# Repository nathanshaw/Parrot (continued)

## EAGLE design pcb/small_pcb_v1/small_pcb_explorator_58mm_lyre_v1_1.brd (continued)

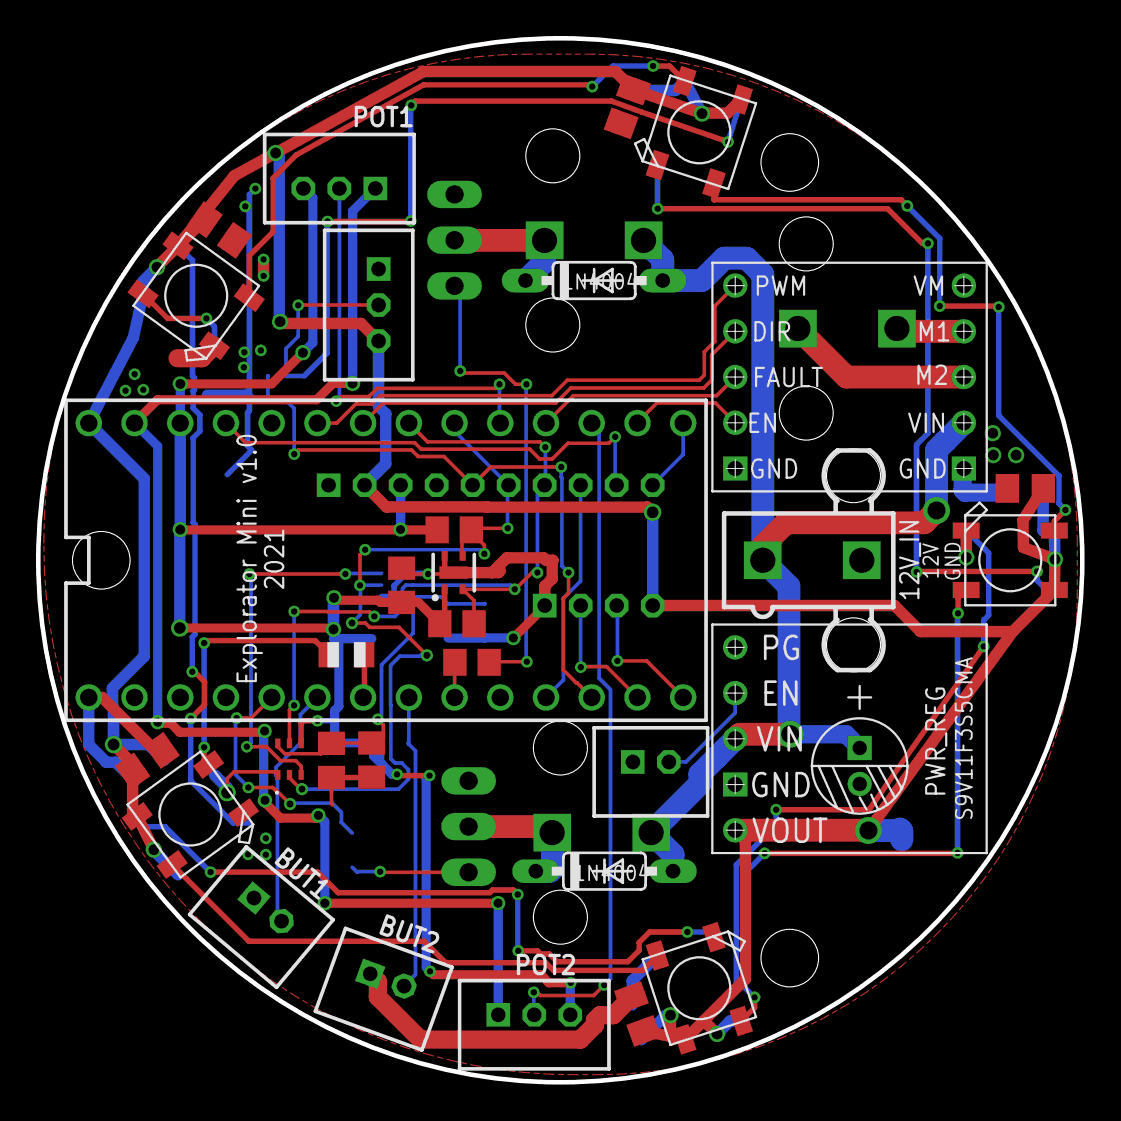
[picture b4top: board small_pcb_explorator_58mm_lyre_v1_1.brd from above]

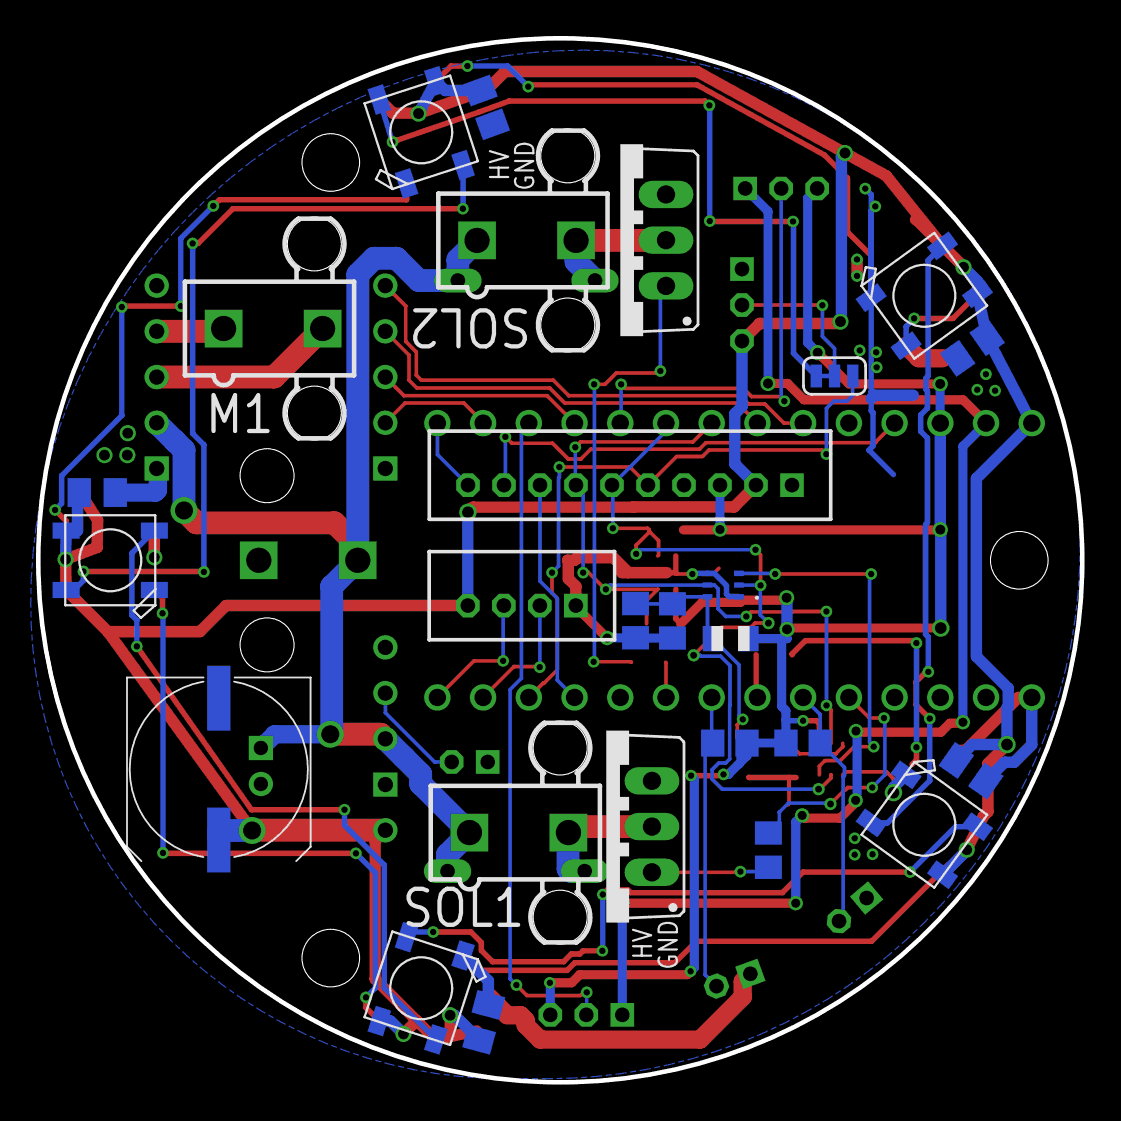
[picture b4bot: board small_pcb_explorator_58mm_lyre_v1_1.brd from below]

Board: 2 copper layers, 58.0 x 58.0 mm, 58 parts (26 on the bottom side), 45 nets.

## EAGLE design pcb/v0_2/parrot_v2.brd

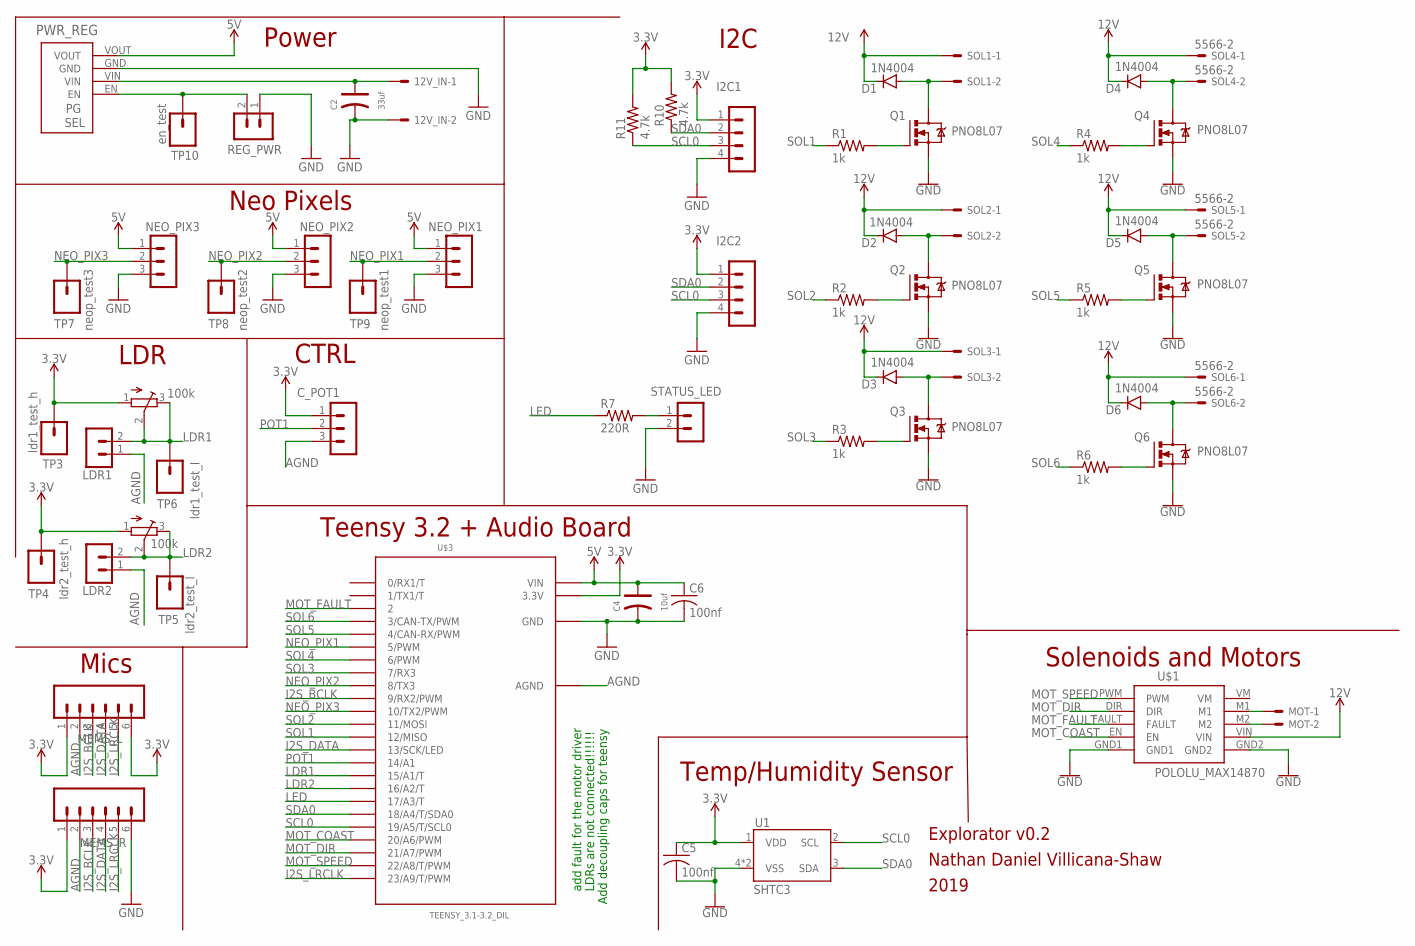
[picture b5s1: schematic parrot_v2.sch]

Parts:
12V_IN: 5566-2
C2: 33uf; PC-D5.3MM
C4: 10uf; PC-D5.3MM
C5, C6: 100nf; C2012
C_POT1: B3B-PH-K
D1, D2, D3, D4, D5, D6: 1N4004; DIODE-1N4001
I2C1, I2C2: B4B-PH-K
LDR1, LDR2: B2B-PH-K
MEMS_L: CONN_06POLAR; MOLEX-1X6
MEMS_R: CONN_06POLAR; MOLEX-1X6
MOT: 5566-2
NEO_PIX1, NEO_PIX2, NEO_PIX3: B3B-PH-K
PWR_REG: S9V11F5S6CMA_MISSINIG_PINS; S9V11F3S5CMA_MISSING_PINS
Q1, Q2, Q3, Q4, Q5, Q6: PNO8L07; TO220BV
R1, R2, R3, R4, R5, R6: 1k; M1206
R7: 220R; M1206
R10, R11: 4.7k; M1206
REG_PWR: B2B-PH-K
SOL1, SOL2, SOL3, SOL4, SOL5, SOL6: 5566-2
STATUS_LED: B2B-PH-K
TM1, TM2: 100k; TC33X
TP3: ldr1_test_h; 1X01
TP4: ldr2_test_h; 1X01
TP5: ldr2_test_l; 1X01
TP6: ldr1_test_l; 1X01
TP7: neop_test3; 1X01
TP8: neop_test2; 1X01
TP9: neop_test1; 1X01
TP10: en_test; 1X01
U1: SHTC3
U$1: POLOLU_MAX14870
U$3: TEENSY_3.1-3.2_DIL; TEENSY_3.0-3.2&LC_DIL

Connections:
3.3V: C5.1, C_POT1.1, I2C1.1, I2C2.1, MEMS_L.1, MEMS_L.6, MEMS_R.1, R10.2, R11.2, TM1.1 (A), TM2.1 (A), TP3.1, TP4.1, U1.1 (VDD), U$3.3.3V
5V: C4.+, C6.1, NEO_PIX1.1, NEO_PIX2.1, NEO_PIX3.1, PWR_REG.VOUT, U$3.VIN
12V: 12V_IN.1, C2.+, D1.C, D2.C, D3.C, D4.C, D5.C, D6.C, PWR_REG.VIN, SOL1.1, SOL2.1, SOL3.1, SOL4.1, SOL5.1, SOL6.1, U$1.VIN
AGND: C_POT1.3, LDR1.1, LDR2.1, MEMS_L.2, MEMS_R.2, U$3.AGND
GND: 12V_IN.2, C2.-, C4.-, C5.2, C6.2, I2C1.4, I2C2.4, MEMS_R.6, NEO_PIX1.3, NEO_PIX2.3, NEO_PIX3.3, PWR_REG.GND, Q1.S, Q2.S, Q3.S, Q4.S, Q5.S, Q6.S, REG_PWR.1, STATUS_LED.2, U1.4 (VSS), U1.5 (VSS), U$1.GND1, U$1.GND2, U$3.GND
I2S_BCLK: MEMS_L.3, MEMS_R.3, U$3.9 (9/RX2/PWM)
I2S_DATA: MEMS_L.4, MEMS_R.4, U$3.13 (13/SCK/LED)
I2S_LRCLK: MEMS_L.5, MEMS_R.5, U$3.23/A9 (23/A9/T/PWM)
LDR1: LDR1.2, TM1.2 (S), TM1.3 (E), TP6.1, U$3.15/A1 (15/A1/T)
LDR2: LDR2.2, TM2.2 (S), TM2.3 (E), TP5.1, U$3.16/A2 (16/A2/T)
LED: R7.1, U$3.17/A3 (17/A3/T)
MOT_COAST: U$1.EN, U$3.20/A6 (20/A6/PWM)
MOT_DIR: U$1.DIR, U$3.21/A7 (21/A7/PWM)
MOT_FAULT: U$1.FAULT, U$3.2
MOT_SPEED: U$1.PWM, U$3.22/A8 (22/A8/T/PWM)
unnamed: Q5.G, R5.2
unnamed: D5.A, Q5.D, SOL5.2
unnamed: Q6.G, R6.2
unnamed: Q2.G, R2.2
unnamed: D6.A, Q6.D, SOL6.2
unnamed: R7.2, STATUS_LED.1
unnamed: D2.A, Q2.D, SOL2.2
unnamed: PWR_REG.EN, REG_PWR.2, TP10.1
unnamed: Q3.G, R3.2
unnamed: D3.A, Q3.D, SOL3.2
unnamed: Q4.G, R4.2
unnamed: D4.A, Q4.D, SOL4.2
unnamed: Q1.G, R1.2
unnamed: D1.A, Q1.D, SOL1.2
unnamed: MOT.2, U$1.M2
unnamed: MOT.1, U$1.M1
NEO_PIX1: NEO_PIX1.2, TP9.1, U$3.5 (5/PWM)
NEO_PIX2: NEO_PIX2.2, TP8.1, U$3.8 (8/TX3)
NEO_PIX3: NEO_PIX3.2, TP7.1, U$3.10 (10/TX2/PWM)
POT1: C_POT1.2, U$3.14/A0 (14/A1)
SCL0: I2C1.3, I2C2.3, R11.1, U1.2 (SCL), U$3.19/A5 (19/A5/T/SCL0)
SDA0: I2C1.2, I2C2.2, R10.1, U1.3 (SDA), U$3.18/A4 (18/A4/T/SDA0)
SOL1: R1.1, U$3.12 (12/MISO)
SOL2: R2.1, U$3.11 (11/MOSI)
SOL3: R3.1, U$3.7 (7/RX3)
SOL4: R4.1, U$3.6 (6/PWM)
SOL5: R5.1, U$3.4 (4/CAN-RX/PWM)
SOL6: R6.1, U$3.3 (3/CAN-TX/PWM)

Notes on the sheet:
Neo Pixels
LDR
I2C
Solenoids and Motors
Teensy 3.2 + Audio Board
Mics
Power
Temp/Humidity Sensor
CTRL
add fault for the motor driver
LDRs are not connected!!!!!!
Add decoupling caps for teensy
Explorator v0.2
Nathan Daniel Villicana-Shaw
2019

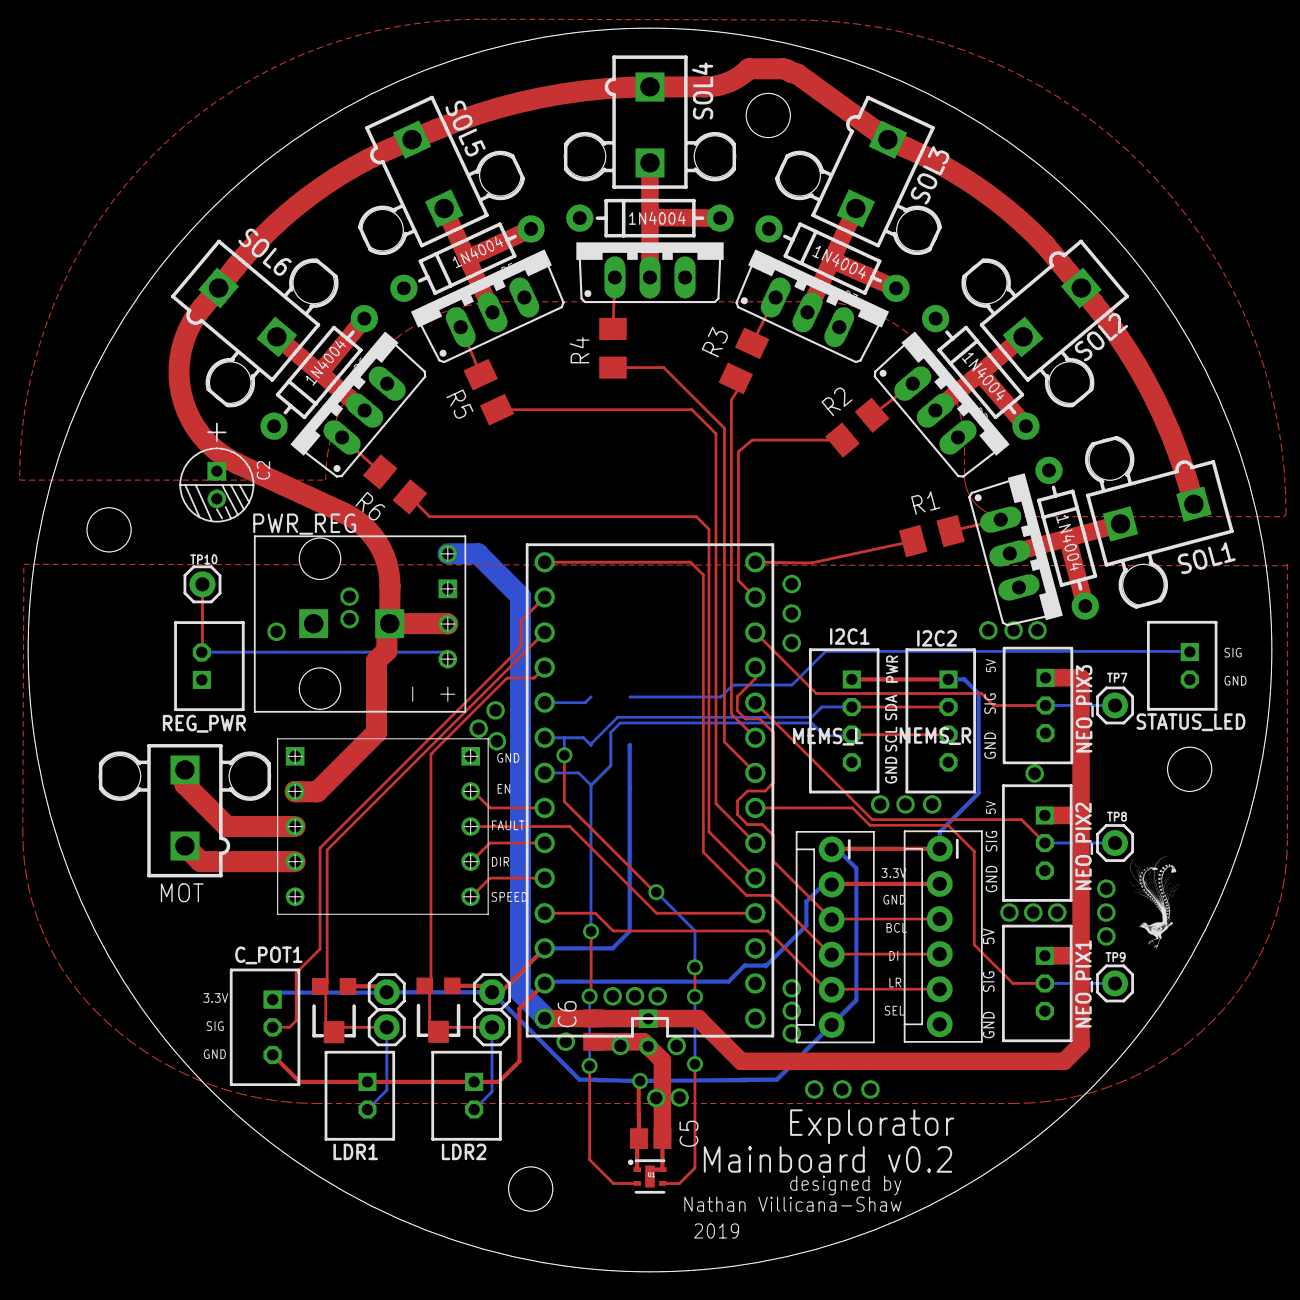
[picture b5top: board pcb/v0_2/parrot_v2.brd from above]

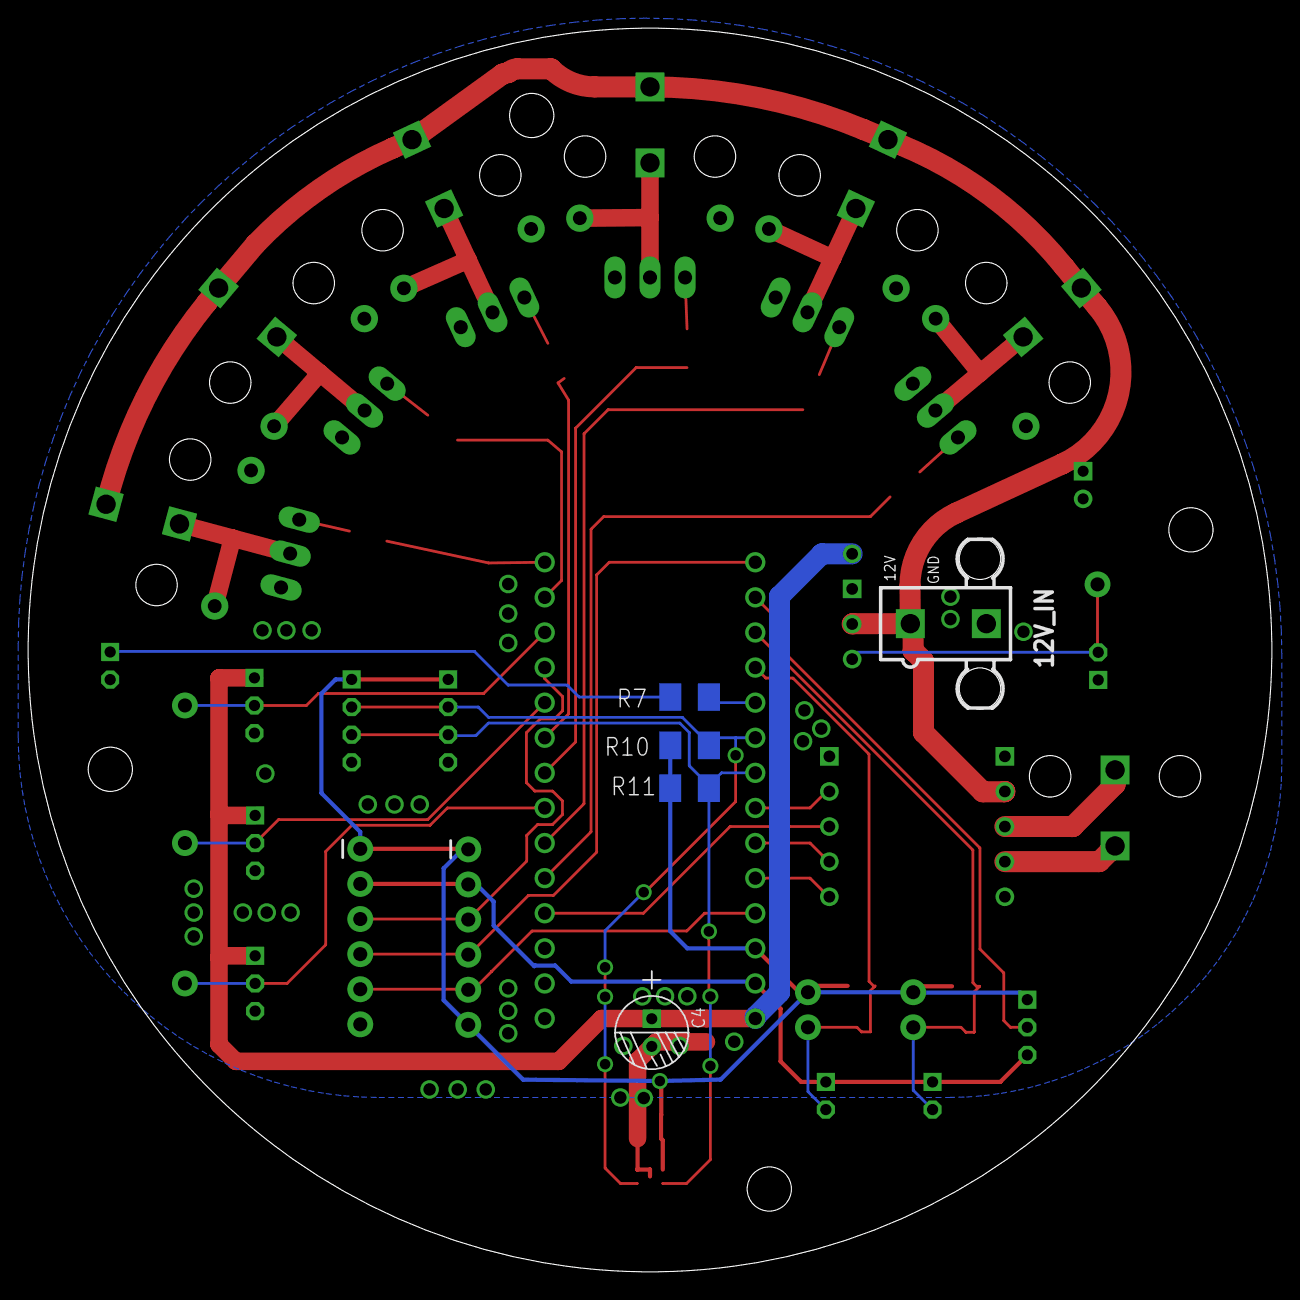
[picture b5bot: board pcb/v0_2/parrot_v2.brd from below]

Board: 2 copper layers, 90.0 x 90.0 mm, 59 parts (5 on the bottom side), 43 nets.

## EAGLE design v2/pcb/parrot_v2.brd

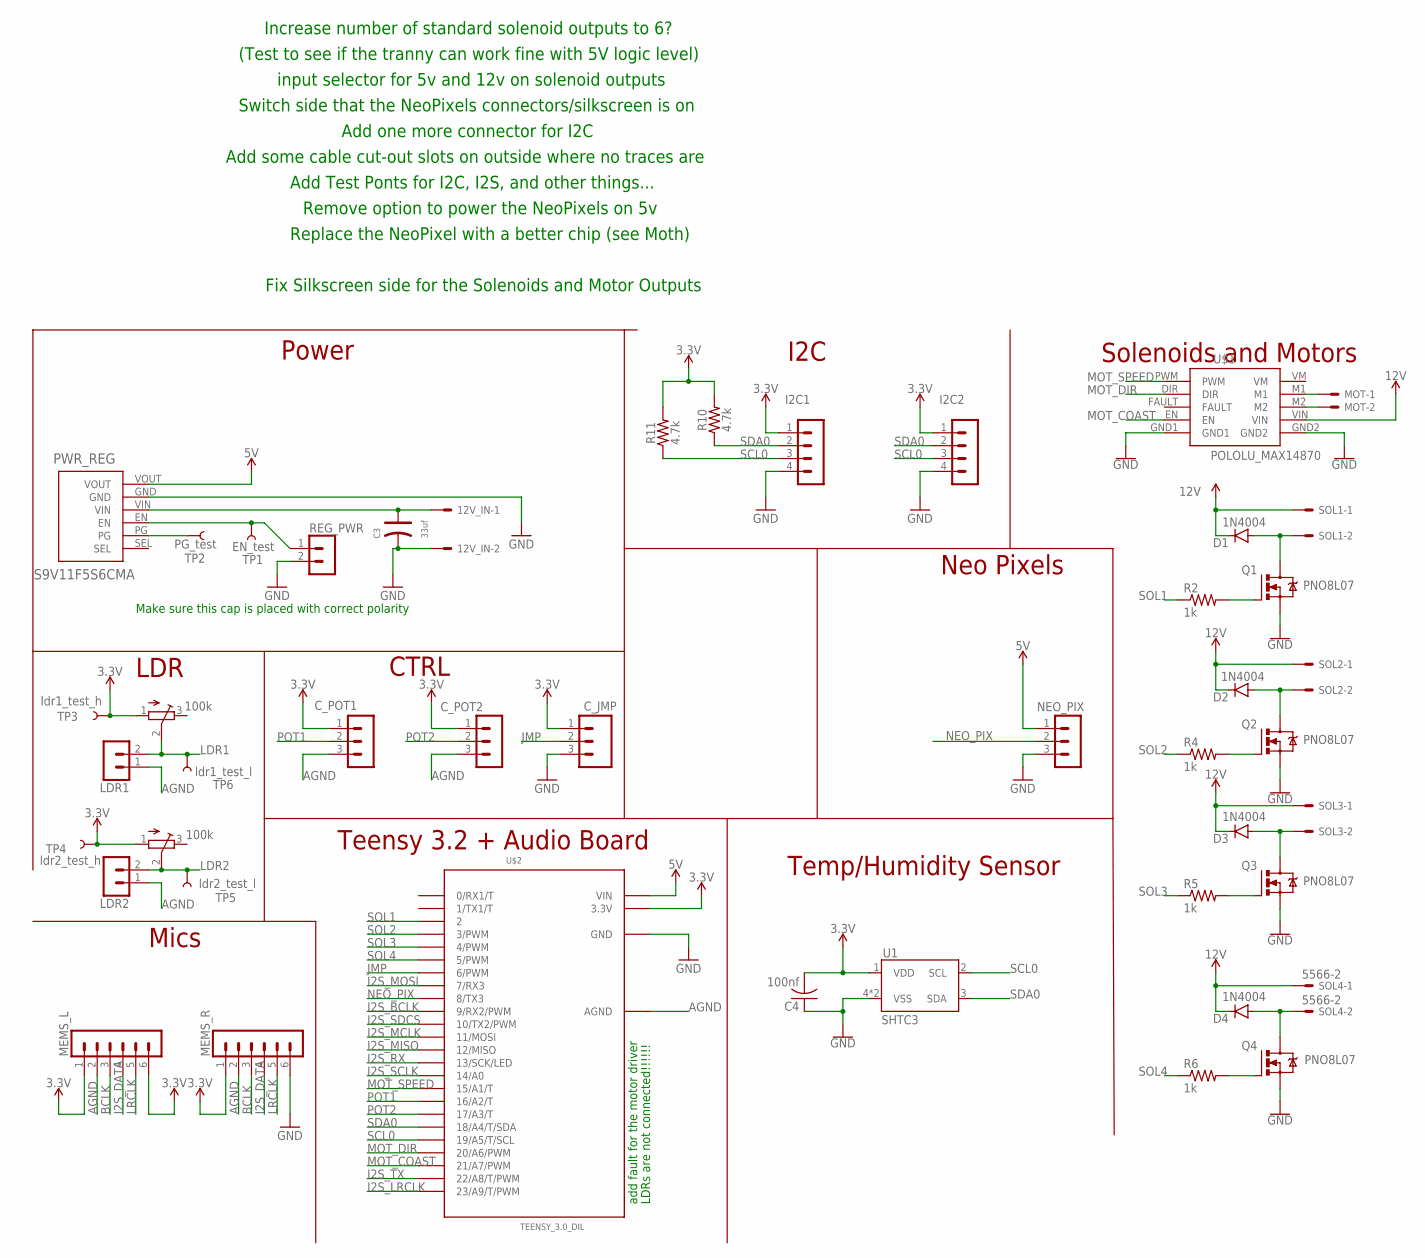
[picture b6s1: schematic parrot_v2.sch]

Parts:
12V_IN: 5566-2
C3: 33uf; PC-D5.3MM
C4: 100nf; C2012
C_JMP: CONN_03; 1X03
C_POT1, C_POT2: B3B-PH-K
D1, D2, D3, D4: 1N4004; DIODE-1N4001
I2C1, I2C2: B4B-PH-K
LDR1, LDR2: B2B-PH-K
MEMS_L: B6B-PH-K
MEMS_R: B6B-PH-K
MOT: 5566-2
NEO_PIX: B3B-PH-K
PWR_REG: S9V11F5S6CMA; S9V11F3S5CMA
Q1, Q2, Q3, Q4: PNO8L07; TO220BV
R2, R4, R5, R6: 1k; AXIAL-0.3
R10, R11: 4.7k; AXIAL-0.3
REG_PWR: B2B-PH-K
SOL1, SOL2, SOL3, SOL4: 5566-2
TM1, TM2: 100k; TC33X
TP1: EN_test; TP_15TH
TP2: PG_test; TP_15TH
TP3: ldr1_test_h; TP_15TH
TP4: ldr2_test_h; TP_15TH
TP5: ldr2_test_l; TP_15TH
TP6: ldr1_test_l; TP_15TH
U1: SHTC3
U$1: POLOLU_MAX14870
U$2: TEENSY_3.0_DIL; TEENSY_3.0-3.2&LC_DIL

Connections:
3.3V: C4.2, C_JMP.1, C_POT1.1, C_POT2.1, I2C1.1, I2C2.1, MEMS_L.1, MEMS_L.6, MEMS_R.1, R10.P$2 (2), R11.P$2 (2), TM1.1 (A), TM2.1 (A), TP3.P$1, TP4.P$1, U1.1 (VDD), U$2.3.3V
5V: NEO_PIX.1, PWR_REG.VOUT, U$2.VIN
12V: 12V_IN.1, C3.+, D1.C, D2.C, D3.C, D4.C, PWR_REG.VIN, SOL1.1, SOL2.1, SOL3.1, SOL4.1, U$1.VIN
AGND: C_POT1.3, C_POT2.3, LDR1.1, LDR2.1, MEMS_L.2, MEMS_R.2, U$2.AGND
BCLK: MEMS_L.3, MEMS_R.3
GND: 12V_IN.2, C3.-, C4.1, C_JMP.3, I2C1.4, I2C2.4, MEMS_R.6, NEO_PIX.3, PWR_REG.GND, Q1.S, Q2.S, Q3.S, Q4.S, REG_PWR.2, U1.4 (VSS), U1.5 (VSS), U$1.GND2, U$2.GND
I2S_BCLK: U$2.9 (9/RX2/PWM)
I2S_DATA: MEMS_L.4, MEMS_R.4
I2S_LRCLK: U$2.23/A9 (23/A9/T/PWM)
I2S_MCLK: U$2.11 (11/MOSI)
I2S_MISO: U$2.12 (12/MISO)
I2S_MOSI: U$2.7 (7/RX3)
I2S_RX: U$2.13 (13/SCK/LED)
I2S_SCLK: U$2.14/A0
I2S_SDCS: U$2.10 (10/TX2/PWM)
I2S_TX: U$2.22/A8 (22/A8/T/PWM)
JMP: C_JMP.2, U$2.6 (6/PWM)
LDR1: LDR1.2, TM1.2 (S), TP6.P$1
LDR2: LDR2.2, TM2.2 (S), TP5.P$1
LRCLK: MEMS_L.5, MEMS_R.5
MOT_COAST: U$1.EN, U$2.21/A7 (21/A7/PWM)
MOT_DIR: U$1.DIR, U$2.20/A6 (20/A6/PWM)
MOT_SPEED: U$1.PWM, U$2.15/A1 (15/A1/T)
unnamed: PWR_REG.PG, TP2.P$1
unnamed: Q2.G, R4.P$2 (2)
unnamed: D2.A, Q2.D, SOL2.2
unnamed: PWR_REG.EN, REG_PWR.1, TP1.P$1
unnamed: Q3.G, R5.P$2 (2)
unnamed: D3.A, Q3.D, SOL3.2
unnamed: Q4.G, R6.P$2 (2)
unnamed: D4.A, Q4.D, SOL4.2
unnamed: Q1.G, R2.P$2 (2)
unnamed: D1.A, Q1.D, SOL1.2
unnamed: MOT.2, U$1.M2
unnamed: MOT.1, U$1.M1
NEO_PIX: NEO_PIX.2, U$2.8 (8/TX3)
POT1: C_POT1.2, U$2.16/A2 (16/A2/T)
POT2: C_POT2.2, U$2.17/A3 (17/A3/T)
SCL0: I2C1.3, I2C2.3, R11.P$1 (1), U1.2 (SCL), U$2.19/A5 (19/A5/T/SCL)
SDA0: I2C1.2, I2C2.2, R10.P$1 (1), U1.3 (SDA), U$2.18/A4 (18/A4/T/SDA)
SOL1: R2.P$1 (1), U$2.2
SOL2: R4.P$1 (1), U$2.3 (3/PWM)
SOL3: R5.P$1 (1), U$2.4 (4/PWM)
SOL4: R6.P$1 (1), U$2.5 (5/PWM)

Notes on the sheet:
Neo Pixels
LDR
I2C
Solenoids and Motors
Teensy 3.2 + Audio Board
Mics
Power
Make sure this cap is placed with correct polarity
Temp/Humidity Sensor
CTRL
add fault for the motor driver
LDRs are not connected!!!!!!
Fix Silkscreen side for the Solenoids and Motor Outputs
Replace the NeoPixel with a better chip (see Moth)
Remove option to power the NeoPixels on 5v
Add Test Ponts for I2C, I2S, and other things...
Add some cable cut-out slots on outside where no traces are
Add one more connector for I2C
Switch side that the NeoPixels connectors/silkscreen is on
input selector for 5v and 12v on solenoid outputs
(Test to see if the tranny can work fine with 5V logic level)
Increase number of standard solenoid outputs to 6?

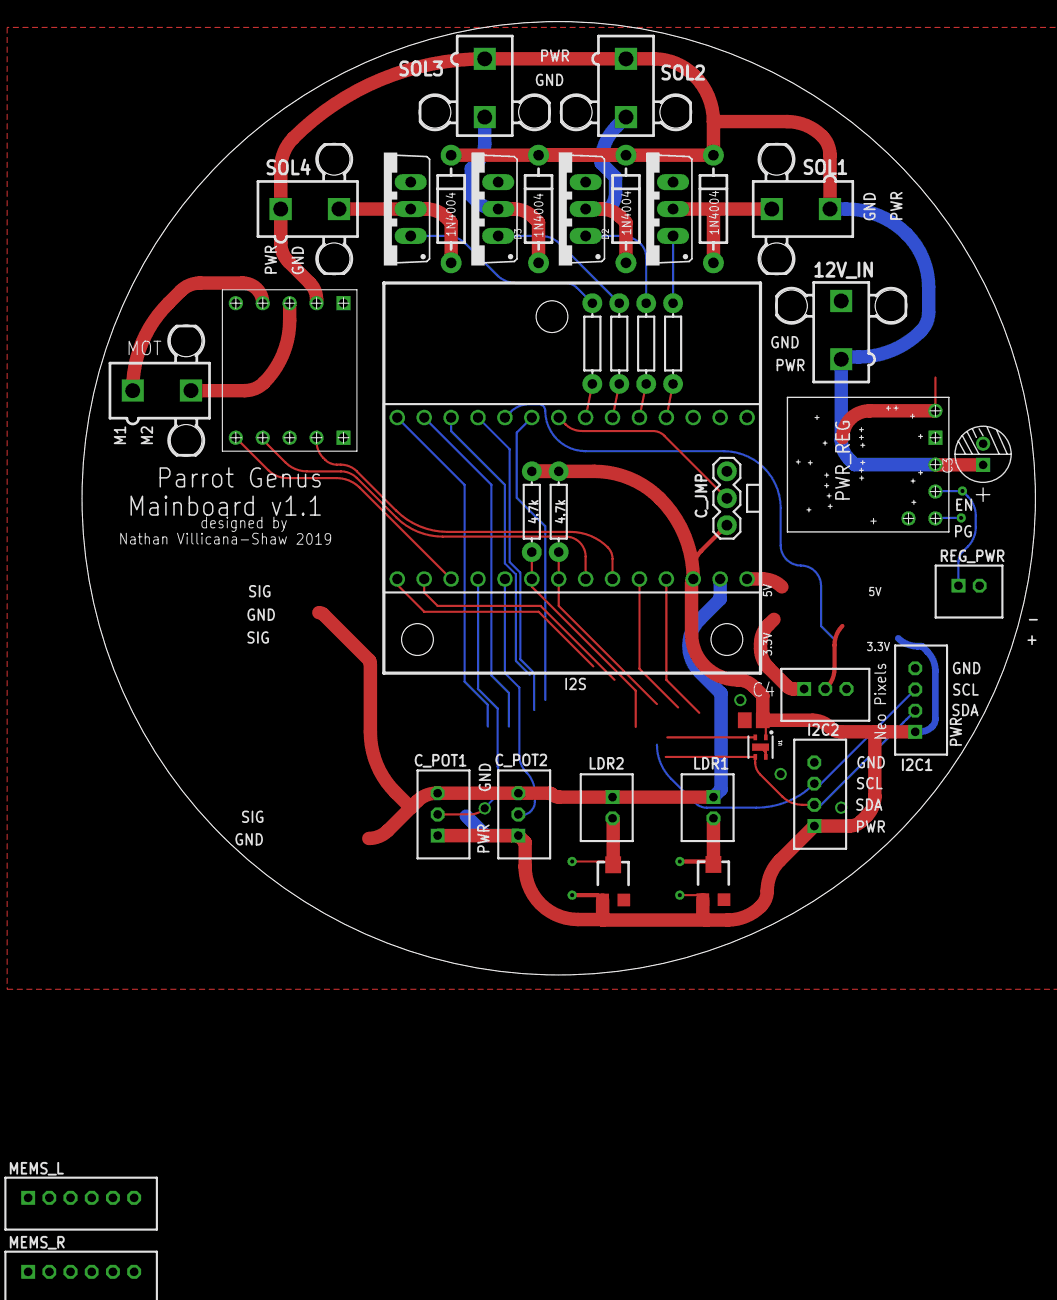
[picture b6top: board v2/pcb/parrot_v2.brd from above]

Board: 2 copper layers, 90.0 x 90.0 mm, 45 parts (0 on the bottom side), 35 nets.

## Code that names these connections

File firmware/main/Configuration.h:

#ifndef __EXPLORATOR_CONFIGURATION_H__
#define __EXPLORATOR_CONFIGURATION_H__
///////////////////////////////////////////////////////////////////////////////////////
/////////////////////////////////// Hardware and Software Settings ////////////////////
///////////////////////////////////////////////////////////////////////////////////////
#define HV_MAJOR       1
#define HV_MINOR       0
#define SV_MAJOR       0
#define SV_MINOR       0
#define SV_REVISION    1
///////////////////////////////////////////////////////////////////////////////////////
/////////////////////////////////// Neopixel LEDs /////////////////////////////////////
///////////////////////////////////////////////////////////////////////////////////////
// Which pin on the Arduino is connected to the NeoPixels? 8 for old board
#define LED1_PIN 5
// note that if the second LED channel is used the teensy needs to be overclocked to 120 MHz
#define LED2_PIN 8
#define LED3_PIN 10

// what the names of the neopixel strips will be
#define LED1_NAME      "small"
#define LED2_NAME      "medium"
#define LED3_NAME      "large"

// How many NeoPixels are attached to the Arduino?
// if no LEDs are connected to the line then set this to 0
#define LED1_COUNT 16
#define LED2_COUNT 16
#define LED3_COUNT 16

#if LED1_COUNT > 0
#define LED1_ACTIVE     true
#else
#define LED1_ACTIVE     false
#endif //LED1_COUNT

#if LED2_COUNT > 0
#define LED2_ACTIVE     true
#else
#define LED2_ACTIVE     false
#endif //LED2_COUNT

#if LED3_COUNT > 0
#define LED3_ACTIVE     true
#else
#define LED3_ACTIVE     false
#endif //LED3_COUNT

const uint16_t max_led_count = max(max(LED1_COUNT, LED2_COUNT), LED3_COUNT);

byte drawingMemory[3][max_led_count * 3];       //  3 bytes per LED
DMAMEM byte displayMemory[3][max_led_count * 12]; // 12 bytes per LED

const uint8_t num_active_led_channels = LED1_ACTIVE + LED2_ACTIVE + LED3_ACTIVE;

///////////////////////////////////////////////////////////////////////////////////////
////////////////////////////// H-Bridge Motors  ///////////////////////////////////////
///////////////////////////////////////////////////////////////////////////////////////

# if HV_MAJOR == 1
#define NUM_MOTORS            3

#define MOT1_ACTIVE           true
#define MOT1_DIR_PIN          26
#define MOT1_PWM_PIN          25
#define MOT1_EN_PIN           28
#define MOT1_FAULT_PIN        27

#define MOT2_ACTIVE           false
#define MOT2_DIR_PIN          29
#define MOT2_PWM_PIN          32
#define MOT2_EN_PIN           31
#define MOT2_FAULT_PIN        30

#define MOT3_ACTIVE           false
#define MOT3_DIR_PIN          21
#define MOT3_PWM_PIN          20
#define MOT3_EN_PIN           2
#define MOT3_FAULT_PIN        22

const bool active_motors[NUM_MOTORS] = {MOT1_ACTIVE, MOT2_ACTIVE, MOT3_ACTIVE};

#endif // HV_MAJOR



///////////////////////////////////////////////////////////////////////////////////////
////////////////////////////// Solenoid Actuators /////////////////////////////////////
///////////////////////////////////////////////////////////////////////////////////////
// this is how long in MS to wait after the dampener is removed before striking with solenoid
#define DAMPENER_DELAY 10

# if HV_MAJOR == 1
#define NUM_SOLENOIDS 9
#define SOL1_PIN 3
#define SOL2_PIN 4
#define SOL3_PIN 6
#define SOL4_PIN 12
#define SOL5_PIN 11
#define SOL6_PIN 14
#define SOL7_PIN 15
#define SOL8_PIN 16
#define SOL9_PIN 7

#define SOL1_ACTIVE true
#define SOL2_ACTIVE true
#define SOL3_ACTIVE false
#define SOL4_ACTIVE true
#define SOL5_ACTIVE true
#define SOL6_ACTIVE false
#define SOL7_ACTIVE true
#define SOL8_ACTIVE true
#define SOL9_ACTIVE false
#endif // HV_MAJOR

# if HV_MAJOR ==        1
// TODO - something about grouping together the solenoids?

///////////////////////////////////////////////////////////////////////////////////////
////////////////////////////// User Controls //////////////////////////////////////////
///////////////////////////////////////////////////////////////////////////////////////

// in ms, how often will theUI controls update?
#define UI_POLLING_RATE 60
// how much play will the pots have before returning a value?
// good values should range between 0.002 and 0.005
#define POT_PLAY        0.004

// should the UIManager print when the user control elements are changed?
#define P_UIMANAGER     true

///////////////////// Buttons //////////////////////////////////////////////////
#define NUM_BUTTONS     4
#define BUT1_PIN        33
#define BUT2_PIN        A13
#define BUT3_PIN        A12
#define BUT4_PIN        17

// should the values received from the buttons be reversed?
#define BUT1_REVERSE    false
#define BUT2_REVERSE    false
#define BUT3_REVERSE    false
#define BUT4_REVERSE    false

#define BUT1_ACTIVE     true
#define BUT2_ACTIVE     true
#define BUT3_ACTIVE     true
#define BUT4_ACTIVE     true

#define BUT1_PULLUP     false
#define BUT2_PULLUP     false
#define BUT3_PULLUP     false
#define BUT4_PULLUP     false

// what is the name of the button? should reflect what it does
#define BUT1_NAME       "BUT1"
#define BUT2_NAME       "BUT2"
#define BUT3_NAME       "BUT3"
#define BUT4_NAME       "BUT4"

///////////////////// Pots /////////////////////////////////////////////////////
#define NUM_POTS        2
#define POT1_PIN        A11
#define POT2_PIN        A10

#define POT1_ACTIVE     true
#define POT2_ACTIVE     false

// should the values received from the pots be reversed?
#define POT1_REVERSE    true
#define POT2_REVERSE    true

// what is the name of the button? should reflect what it does
#define POT1_NAME       "POT1"
#define POT2_NAME       "POT2"

#endif // HV_MAJOR

///////////////////////////////////////////////////////////////////////////////////////
////////////////////////////// Weather Manager ////////////////////////////////////////
///////////////////////////////////////////////////////////////////////////////////////
#define WM_UPDATE_DELAY                     1000
// what is the threshold that will determine when Humidity shutddown is activated. .50 equates to 50%
#define HUMID_EXTREME_THRESH                95
// what temp is the thrsehold (in c)        
#define TEMP_EXTRME_THRESH                  50
// 0.2 equates to 20% of the threshold, so if the threshold is 100 and 
// this value is 0.2 the Speculator will reactivate once the temperature
// drops to 80 degrees
#define TEMP_HISTORESIS                     0.2

///////////////////////////////////////////////////////////////////////////////////////
////////////////////////////// Lux Manager ////////////////////////////////////////////
///////////////////////////////////////////////////////////////////////////////////////
#define LUX_ADJUSTS_BS                  0
#define LUX_ADJUSTS_MIN_MAX             1
uint8_t LUX_MAPPING_SCHEMA =            LUX_ADJUSTS_MIN_MAX;

// These are determined by the LUX_READINGS, any values se here will just serve as a
// default value which will be overwriten once a lux reading is taken. 
// PLEASE NOTE: the MAX_BRIGHTNEESS is for all three color channels not just a single channel
// so for instance if rgb = 150, 150, 150. that would be limited if the MAX_BRIGHTNESS IS 450
// that makes it so a MAX_BRIGHTNESS is actually 765
uint16_t  MIN_BRIGHTNESS =              0;
uint16_t  MAX_BRIGHTNESS =              765;

#define NIGHT_LUX_THRESHOLD             1.0
// this is the threshold in which anything below will just be treated as the lowest reading
#define LOW_LUX_THRESHOLD               10.0
// when a lux of this level is detected the LEDs will be driven with a brightness scaler of 1.0
#define MID_LUX_THRESHOLD               350.0
#define HIGH_LUX_THRESHOLD              1200.0
#if HV_MAJOR < 3
#define EXTREME_LUX_THRESHOLD           5000.0
#else
#define EXTREME_LUX_THRESHOLD           5000.0
#endif

// on scale of 0-1.0 what is the min multiplier for the user defined brightness scaler
#define BRIGHTNESS_SCALER_MIN           0.05
#define BRIGHTNESS_SCALER_MAX           3.00

uint32_t lux_max_reading_delay =        1000 * 60 * 1;   // every minute
uint32_t lux_min_reading_delay =        1000 * 10;       // ten seconds

#endif // __CONFIGURATION__H__

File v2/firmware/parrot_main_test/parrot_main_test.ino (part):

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//////////////////////////////////////////////////////////////////////////
///////////////////  Solenoids/actuators  ////////////////////////////////
//////////////////////////////////////////////////////////////////////////
#define SOL1_PIN 12
#define SOL2_PIN 11
#define SOL3_PIN 7
#define SOL4_PIN 6
#define SOL5_PIN 4
#define SOL6_PIN 3

const int s_pins[] = {SOL1_PIN, SOL2_PIN, SOL3_PIN, SOL4_PIN, SOL5_PIN, SOL6_PIN};
uint16_t sol_on_time[] = {30, 30, 30, 30, 30, 30};
bool sol_state[] = {false, false, false, false, false, false}; // is the solenoid on or off

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//////////////////////////////////////////////////////////////////////////
// H-Bridge Motor (MAX14870)
// #define LED_PIN 13
#define MOT_DIR_PIN 21
#define MOT_PWM_PIN 22
#define MOT_EN_PIN 20
#define MOT_FAULT_PIN 2
DualMAX14870MotorShield motor(MOT_DIR_PIN, MOT_PWM_PIN, 31, 32, MOT_EN_PIN, MOT_FAULT_PIN); // 31, 32, and 33 are unused pins

void testMotor(unsigned int len) {
  motor.enableDrivers();
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
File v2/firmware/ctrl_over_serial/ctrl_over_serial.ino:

/* Mechatronic Creatures
   "Bowl Bot" Genus
   using the Adafruit Huzzah ESP8266 Microcontroller


*/
#include "SparkFun_SHTC3.h"
#include <DualMAX14870MotorShield.h>
#include <Adafruit_NeoPixel.h>
#ifdef __AVR__
#include <avr/power.h> // Required for 16 MHz Adafruit Trinket
#endif

// Which pin on the Arduino is connected to the NeoPixels?
#define LED_PIN_1 5
#define LED_PIN_1 8
#define LED_PIN_1 10

// How many NeoPixels are attached to the Arduino?
#define LED_COUNT 10

// Declare our NeoPixel strip object:
Adafruit_NeoPixel strip(LED_COUNT, LED_PIN_1, NEO_GRB + NEO_KHZ800);
// Argument 1 = Number of pixels in NeoPixel strip
// Argument 2 = Arduino pin number (most are valid)
// Argument 3 = Pixel type flags, add together as needed:
//   NEO_KHZ800  800 KHz bitstream (most NeoPixel products w/WS2812 LEDs)
//   NEO_KHZ400  400 KHz (classic 'v1' (not v2) FLORA pixels, WS2811 drivers)
//   NEO_GRB     Pixels are wired for GRB bitstream (most NeoPixel products)
//   NEO_RGB     Pixels are wired for RGB bitstream (v1 FLORA pixels, not v2)
//   NEO_RGBW    Pixels are wired for RGBW bitstream (NeoPixel RGBW products)

// Solenoids
const int s_pins[] = {12, 11, 7, 6, 4, 3};

// H-Bridge Motor (MAX14870)
#define LED_PIN 13
uint8_t mot_dir = 21;
uint8_t mot_pwm = 22;
uint8_t mot_en = 20;
DualMAX14870MotorShield motor(mot_dir, mot_pwm, 31, 32, mot_en, 33); // 31, 32, and 33 are unused pins

// pots
uint8_t pot = 14;
uint16_t pot_val = 0;

// jumper button
uint8_t jump_but = 6;

// LDR ??!!??!!
uint8_t ldr1 = 15;
uint8_t ldr2 = 16;
uint16_t ldr1_val = 0;
uint16_t ldr2_val = 0;

// temp and humidity
SHTC3 mySHTC3;
double temp = 0.0;
double humidity = 0.0;

void setup() {
  Serial.begin(115200);
  strip.begin();           // INITIALIZE NeoPixel strip object (REQUIRED)
  strip.show();            // Turn OFF all pixels ASAP
  strip.setBrightness(50); // Set BRIGHTNESS to about 1/5 (max = 255)
  delay(2000);
  // put your setup code here, to run once:
  pinMode(s_pins[0], OUTPUT);
  pinMode(s_pins[1], OUTPUT);
  pinMode(s_pins[2], OUTPUT);
  pinMode(s_pins[3], OUTPUT);
  pinMode(s_pins[4], OUTPUT);
  pinMode(s_pins[5], OUTPUT);

  digitalWrite(s_pins[0], LOW);
  digitalWrite(s_pins[1], LOW);
  digitalWrite(s_pins[2], LOW);
  digitalWrite(s_pins[3], LOW);
  digitalWrite(s_pins[4], LOW);
  digitalWrite(s_pins[5], LOW);

  pinMode(ldr1, INPUT);
  pinMode(ldr2, INPUT);
  
  // temp and humidity sensor
  errorDecoder(mySHTC3.begin());
  Wire.setClock(400000);
  if (mySHTC3.passIDcrc)                                      // Whenever data is received the associated checksum is calculated and verified so you can be sure the data is true
  { // The checksum pass indicators are: passIDcrc, passRHcrc, and passTcrc for the ID, RH, and T readings respectively
    Serial.print("ID Passed Checksum. ");
    Serial.print("Device ID: 0b");
    Serial.print(mySHTC3.ID, BIN);                       // The 16-bit device ID can be accessed as a member variable of the object
  }
  else
  {
    Serial.print("ID Checksum Failed. ");
  }

  //motor.flipM1(true); // if the direction of the motor needs to be flipped
  Serial.println("Finshed Setting up");
  Serial.println("||||||||||||||||||||||||||||||||||||||||||||||||||||");
  Serial.println("Welcome to the Parrot Test Program");
  Serial.println("0-5 to pulse solenoids 1-4");
  Serial.println("b to move motor backwards");
  Serial.println("f to move motor forwards");
  Serial.println("6 to read and print pot values");
  Serial.println("7 to read and print the LDR values");
  Serial.println("8 to read and print the temp/humidity sensor values");
  Serial.println("9 to read and print the jumper button value");
  Serial.println("||||||||||||||||||||||||||||||||||||||||||||||||||||");
}

void loop() {
  // put your main code here, to run repeatedly:
  if (Serial.available() > 0) {
    int incByte = Serial.read() - 48;
    Serial.print("incbyte : ");
    Serial.println(incByte);
    if (incByte > -1 && incByte < 6) {
      Serial.print("pulsing solenoid output #");
      Serial.println(incByte);
      digitalWrite(s_pins[incByte], HIGH);
      strip.setPixelColor(incByte, strip.Color(255, 0, 0));
      strip.show();
      delay(50);
      strip.setPixelColor(incByte, strip.Color(0, 0, 0));
      strip.show();
      digitalWrite(s_pins[incByte], LOW);
    }
    else if (incByte == 50) {
      Serial.println("pulse motor backwards");
      motor.enableDrivers();
      // pulse motor "backwards"
      for (int speed = 0; speed >= -400; speed--)
      {
        motor.setM1Speed(speed);
        delay(1);
      }

      for (int speed = -400; speed <= 0; speed++)
      {
        motor.setM1Speed(speed);
        delay(1);
      }
      motor.disableDrivers();
    } else if (incByte == 54) {
      // pulse motor "forward"
      Serial.println("pulse motor forwards");
      motor.enableDrivers();
      for (int speed = 0; speed <= 400; speed++)
      {
        motor.setM1Speed(speed);
        delayMicroseconds(300);
      }

      for (int speed = 400; speed >= 0; speed--)
      {
        motor.setM1Speed(speed);
        delayMicroseconds(300);
      }
      motor.disableDrivers();
    } else if (incByte == 6) { // pot values
      pot_val = analogRead(pot);
      Serial.print("Pot value: ");
      Serial.print(pot_val);
    } else if (incByte == 7) { // LDR values
      Serial.print("LDR : ");
      Serial.print(analogRead(ldr1));
      Serial.print("\t");
      Serial.println(analogRead(ldr2));
    } else if (incByte == 8) { // temp/humidity sensor
      SHTC3_Status_TypeDef result = mySHTC3.update();             // Call "update()" to command a measurement, wait for measurement to complete, and update the RH and T members of the object
      printSHTCInfo();                                                // This function is used to print a nice little line of info to the serial port
      Serial.print("Temp:");
      Serial.print(temp);
      Serial.print("\t Humidity:");
      Serial.println(humidity);
    } else if (incByte == 9) { // Jumper button
      Serial.print("Jumper button value is: ");
      Serial.println(digitalRead(jump_but));
    }
  }
}

///////////////////////
// SHTC3 Utility Functions //
///////////////////////
void printSHTCInfo()
{
  if (mySHTC3.lastStatus == SHTC3_Status_Nominal)             // You can also assess the status of the last command by checking the ".lastStatus" member of the object
  {
    humidity = mySHTC3.toPercent();
    Serial.print("RH = ");
    Serial.print(humidity);                   // "toPercent" returns the percent humidity as a floating point number
    Serial.print("% (checksum: ");
    if (mySHTC3.passRHcrc)                                    // Like "passIDcrc" this is true when the RH value is valid from the sensor (but not necessarily up-to-date in terms of time)
    {
      Serial.print("pass");
    }
    else
    {
      Serial.print("fail");
    }
    Serial.print("), T = ");
    temp = mySHTC3.toDegF();
    Serial.print(temp);                        // "toDegF" and "toDegC" return the temperature as a flaoting point number in deg F and deg C respectively
    Serial.print(" deg F (checksum: ");
    if (mySHTC3.passTcrc)                                       // Like "passIDcrc" this is true when the T value is valid from the sensor (but not necessarily up-to-date in terms of time)
    {
      Serial.print("pass");
    }
    else
    {
      Serial.print("fail");
    }
    Serial.println(")");
  }
  else
  {
    Serial.print("Update failed, error: ");
    errorDecoder(mySHTC3.lastStatus);
    Serial.println();
  }
}

void errorDecoder(SHTC3_Status_TypeDef message)                             // The errorDecoder function prints "SHTC3_Status_TypeDef" resultsin a human-friendly way
{
  switch (message)
  {
    case SHTC3_Status_Nominal : Serial.print("Nominal"); break;
    case SHTC3_Status_Error : Serial.print("Error"); break;
    case SHTC3_Status_CRC_Fail : Serial.print("CRC Fail"); break;
    default : Serial.print("Unknown return code"); break;
  }
}

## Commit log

2019-09-10 added a basic testing program for parrot =)
2019-10-18 added images, zip files and audio tracks to lfs, moved the PCB files into the repo, made a folder for v1 and v2
2019-10-18 added gitattributes
2019-10-19 updated the temp/humidity sensor library and test code being used, moved code which used the old Sparkfun library to a newly created legacy firmware folder
2020-02-04 moving along, added pdf, jpg, and png to git lfs
2020-02-04 added git attributes
2020-03-04 moving to a v 0.0.1 for the code
2020-03-04 removed audio engine and neop manager, as I will be readding them as submodules
2020-03-04 added min/max tracking for peak
2020-05-14 got the code for lyre to compile
2020-07-26 moved some things around in the repo
2020-09-24 moving to a v1
2020-09-24 working to v1 again lol
2020-09-24 updated submodules
2020-09-24 moved luxManager out
2021-03-06 updated some long needed things for the repo
2021-03-09 added a file for the shaker test
2021-03-09 I think i removed git lfs from the repo, not 100% sure though
2021-03-09 removed two gitattributes files
